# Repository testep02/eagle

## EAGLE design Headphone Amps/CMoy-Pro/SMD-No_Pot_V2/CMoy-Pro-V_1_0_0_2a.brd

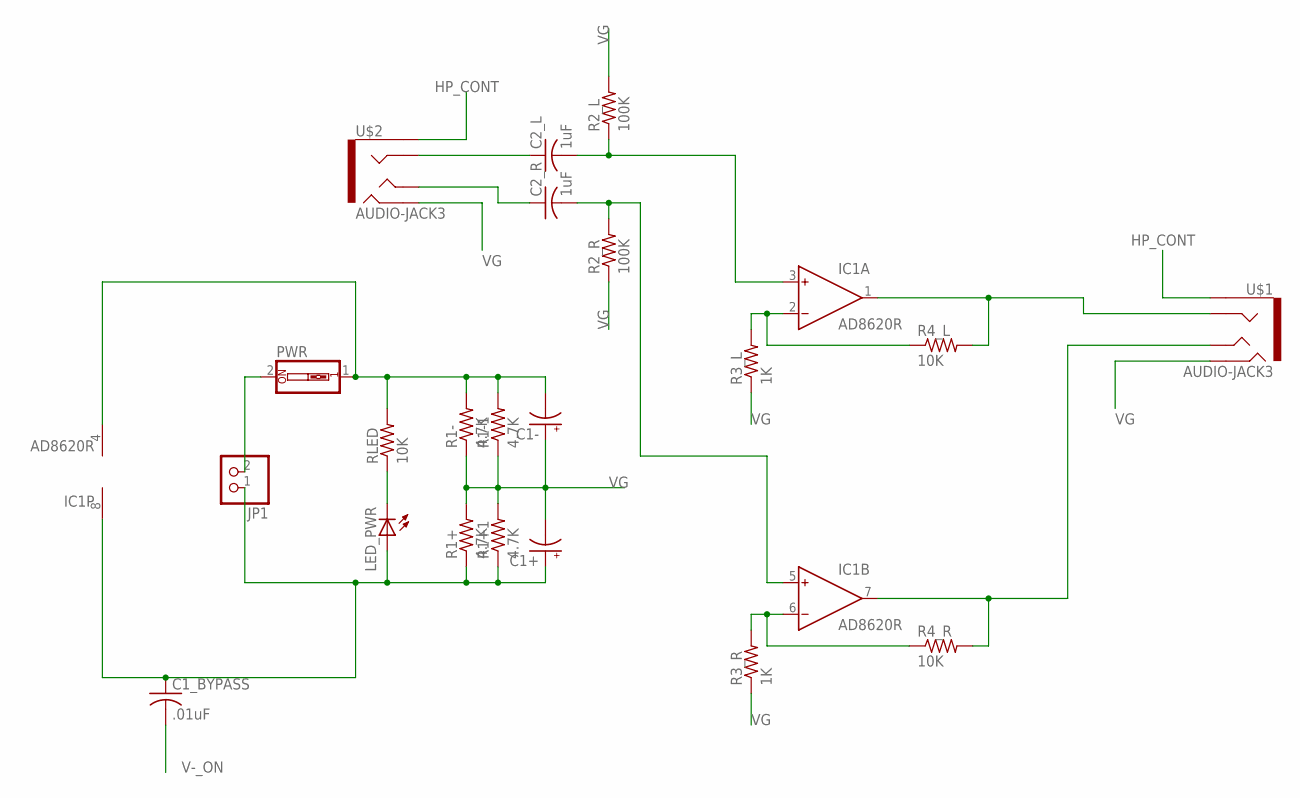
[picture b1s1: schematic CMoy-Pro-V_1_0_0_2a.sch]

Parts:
C1+, C1-: CPOL-US140CLH-0810; 140CLH-0810
C1_BYPASS: .01uF; C0603
C2_L, C2_R: 1uF; C1210
IC1: AD8620R; SO8
JP1: PINHD-1X2; 1X02
LED_PWR: LEDCHIP-LED0603; CHIP-LED0603
PWR: SW_DIP-1; EDG-01
R1+, R1+1, R1-, R1-1: 4.7K; R0603
R2_L, R2_R: 100K; R0603
R3_L, R3_R: 1K; R0603
R4_L, R4_R: 10K; R0603
RLED: 10K; R0603
U$1, U$2: AUDIO-JACK3; AUDIO-JACK-TRRS-SMD

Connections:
HP_CONT: U$1.EARTH, U$2.EARTH
HP_L: C2_R.1, U$2.TIP
HP_R: C2_L.1, U$2.RING1
IN_L: C2_R.2, IC1.5 (IN+), R2_R.2
IN_R: C2_L.2, IC1.3 (IN+), R2_L.1
unnamed: LED_PWR.C, RLED.1
unnamed: IC1.2 (IN-), R3_L.2, R4_L.1
unnamed: IC1.6 (IN-), R3_R.2, R4_R.1
OUT_L: IC1.7 (OUT), R4_R.2, U$1.TIP
OUT_R: IC1.1 (OUT), R4_L.2, U$1.RING1
V+: C1+.+, C1_BYPASS.1, IC1.8 (V+), JP1.1, LED_PWR.A, R1+.1, R1+1.1
V-: JP1.2, PWR.2
V-_ON: C1-.-, C1_BYPASS.2, IC1.4 (V-), PWR.1, R1-.2, R1-1.2, RLED.2
VG: C1+.-, C1-.+, R1+.2, R1+1.2, R1-.1, R1-1.1, R2_L.2, R2_R.1, R3_L.1, R3_R.1, U$1.RING2, U$2.RING2

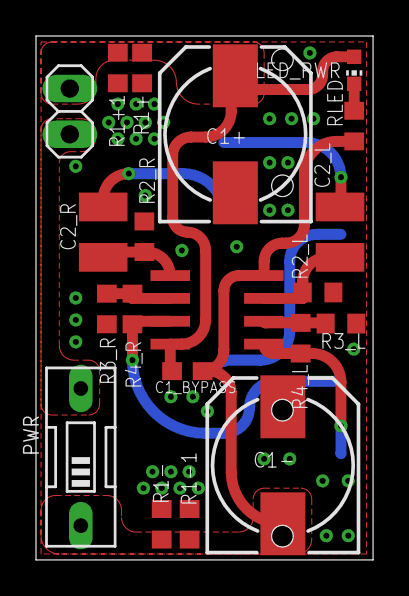
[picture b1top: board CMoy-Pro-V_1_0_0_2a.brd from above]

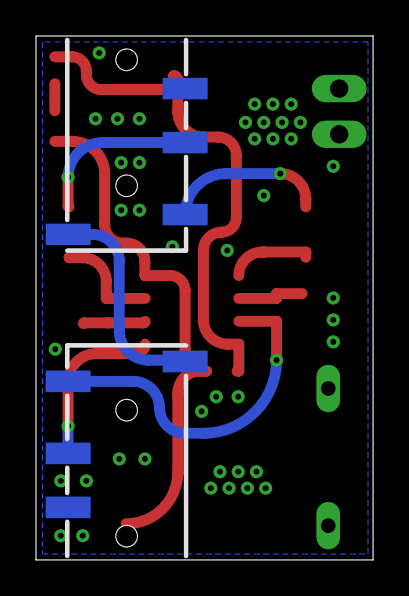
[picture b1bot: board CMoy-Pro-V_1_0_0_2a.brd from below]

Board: 2 copper layers, 18.7 x 29.1 mm, 22 parts (2 on the bottom side), 14 nets.

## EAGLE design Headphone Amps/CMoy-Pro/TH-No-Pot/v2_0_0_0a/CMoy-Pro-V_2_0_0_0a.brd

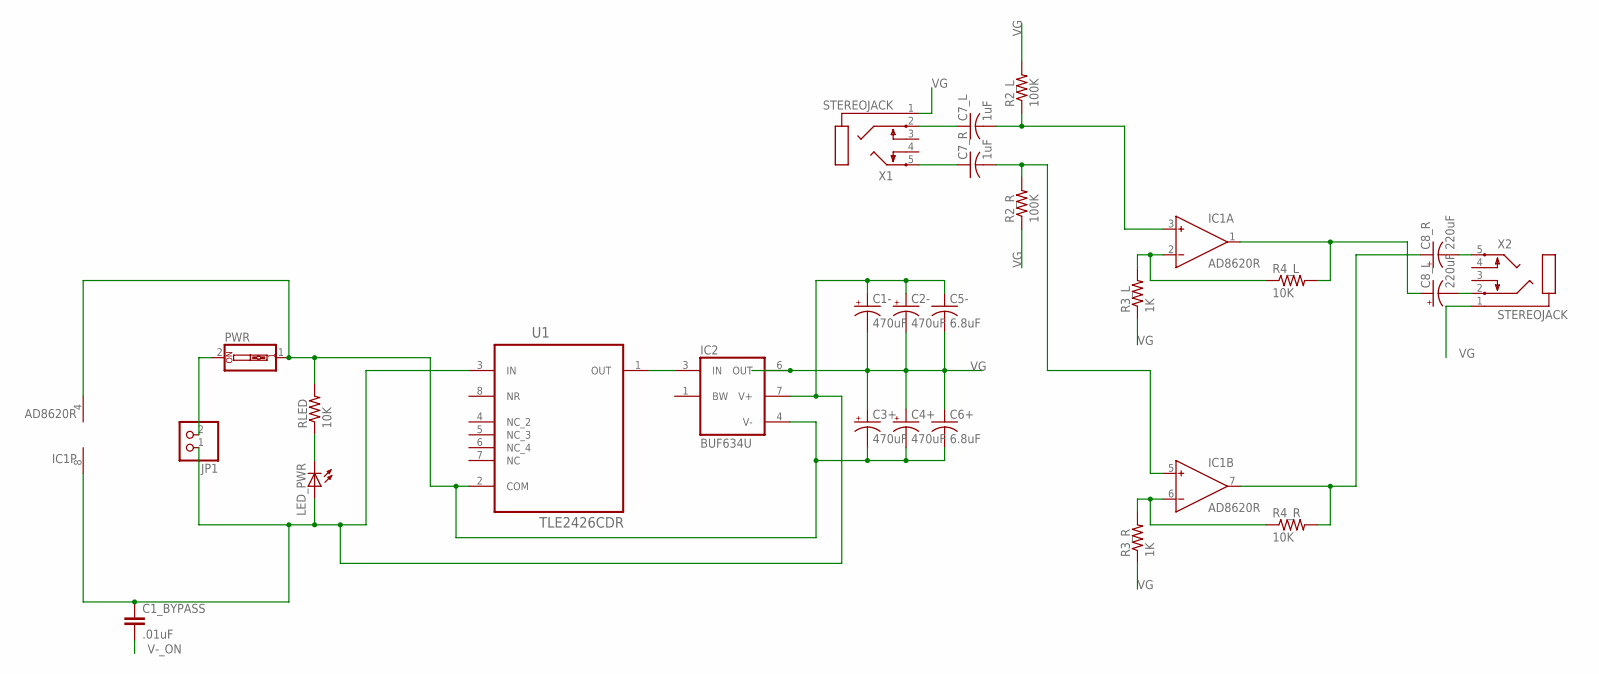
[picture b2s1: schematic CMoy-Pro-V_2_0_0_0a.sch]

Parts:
C1-, C2-, C3+, C4+: 470uF; E3,5-10
C1_BYPASS: .01uF; C0402
C5-, C6+: 6.8uF; C075-042X103
C7_L, C7_R: 1uF; C075-042X103
C8_L, C8_R: 220uF; E3,5-10
IC1: AD8620R; SO8
IC2: BUF634U; SO08
JP1: PINHD-1X2; 1X02
LED_PWR: LED3MM
PWR: SW_DIP-1; EDG-01
R2_L, R2_R: 100K; 0207/7
R3_L, R3_R: 1K; 0207/7
R4_L, R4_R: 10K; 0207/7
RLED: 10K; 0207/7
U1: TLE2426CDR; SOIC127P600X175-8N
X1, X2: STEREOJACK; STX3100

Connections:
IN_R: C7_R.2, IC1.5 (IN+), R2_R.2
unnamed: C7_L.2, IC1.3 (IN+), R2_L.1
unnamed: C8_L.-, X2.2
unnamed: LED_PWR.K (C), RLED.1
unnamed: C7_L.1, X1.2
unnamed: IC1.2 (IN-), R3_L.2, R4_L.1
unnamed: IC1.6 (IN-), R3_R.2, R4_R.1
unnamed: C7_R.1, X1.5
unnamed: C8_R.-, X2.5
unnamed: IC2.3 (IN), U1.1 (OUT)
OUT_L: C8_L.+, IC1.1 (OUT), R4_L.2
OUT_R: C8_R.+, IC1.7 (OUT), R4_R.2
V+: C1-.+, C1_BYPASS.1, C2-.+, C5-.1, IC1.8 (V+), IC2.7 (V+), JP1.1, LED_PWR.A, U1.3 (IN)
V-: JP1.2, PWR.2
V-_ON: C1_BYPASS.2, C3+.-, C4+.-, C6+.2, IC1.4 (V-), IC2.4 (V-), PWR.1, RLED.2, U1.2 (COM)
VG: C1-.-, C2-.-, C3+.+, C4+.+, C5-.2, C6+.1, IC2.6 (OUT), R2_L.2, R2_R.1, R3_L.1, R3_R.1, X1.1, X2.1

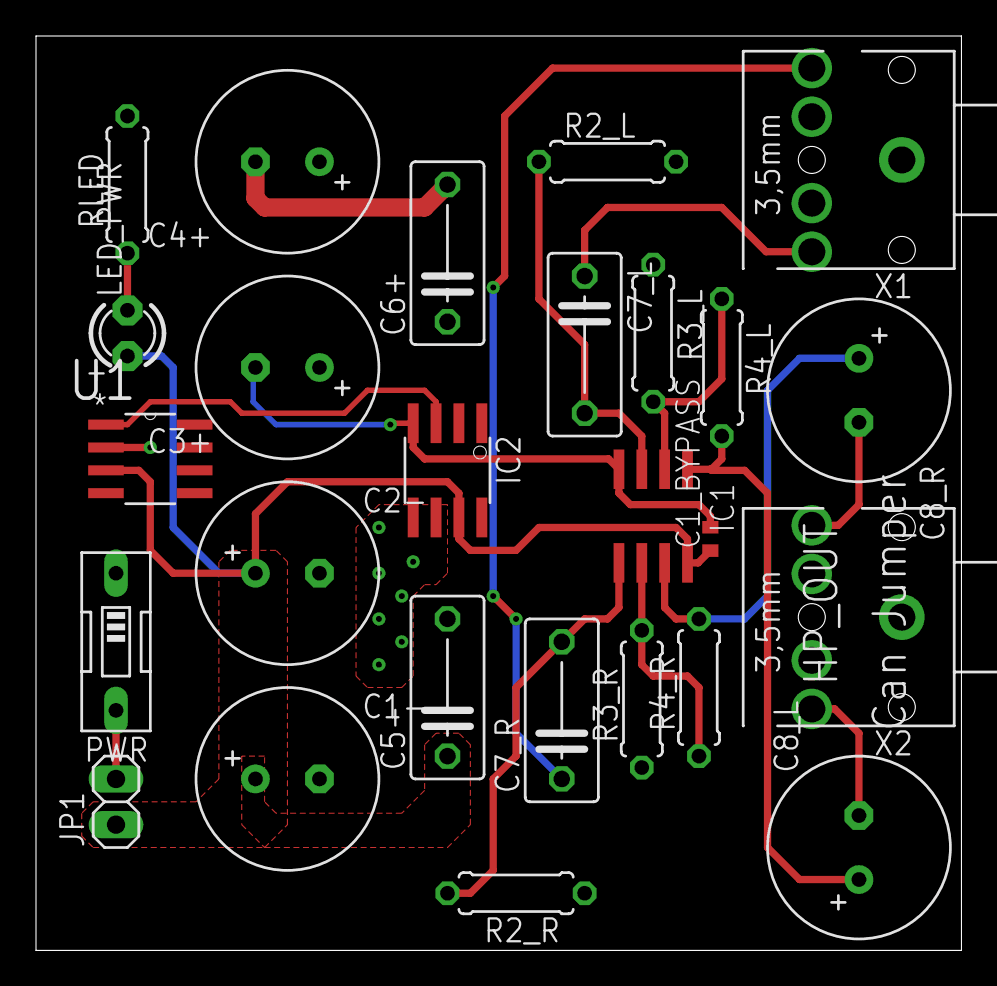
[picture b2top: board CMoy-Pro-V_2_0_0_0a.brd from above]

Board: 2 copper layers, 51.4 x 50.8 mm, 26 parts (0 on the bottom side), 16 nets.

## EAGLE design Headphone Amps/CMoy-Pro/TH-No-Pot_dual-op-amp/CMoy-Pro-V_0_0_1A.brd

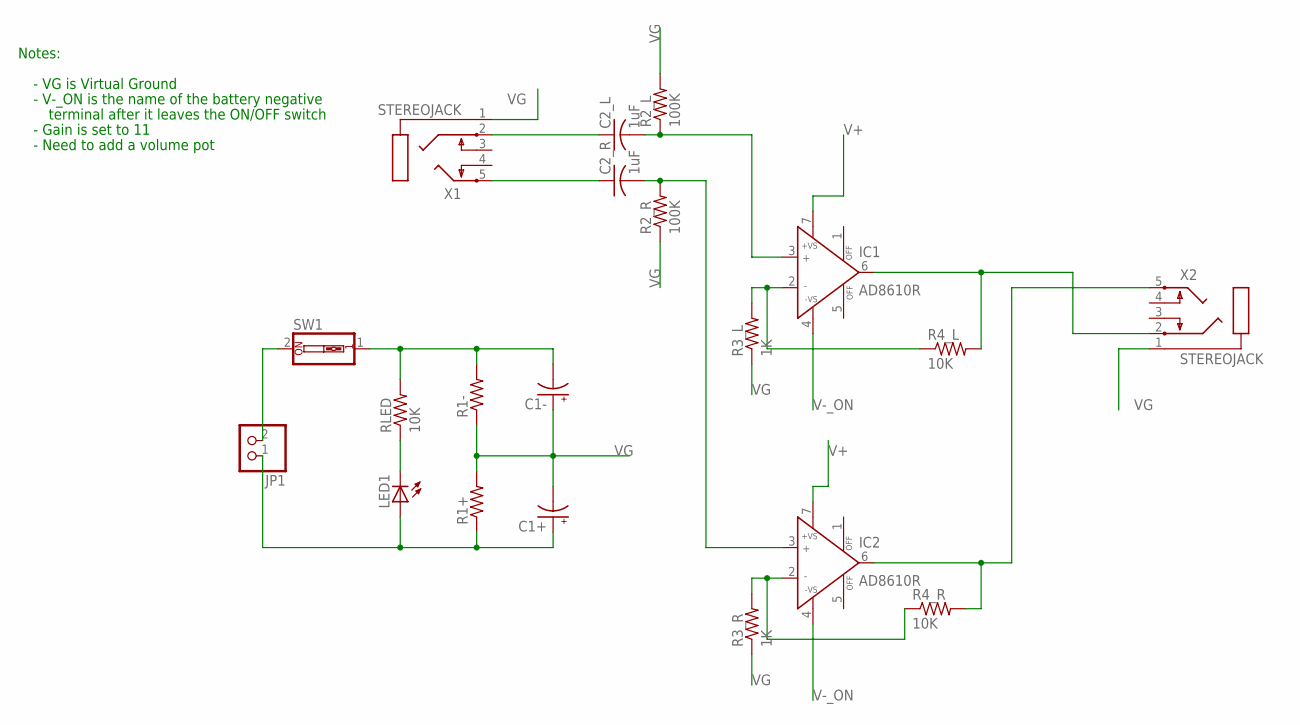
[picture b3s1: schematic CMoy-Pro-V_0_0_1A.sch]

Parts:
C1+, C1-: CPOL-USE2.5-6; E2,5-6
C2_L, C2_R: 1uF; C102-043X133
IC1, IC2: AD8610R; SO8
JP1: PINHD-1X2; 1X02
LED1: LED3MM
R1+, R1-: R-US_0207/7; 0207/7
R2_L, R2_R: 100K; 0207/7
R3_L, R3_R: 1K; 0207/7
R4_L, R4_R: 10K; 0207/7
RLED: 10K; 0207/7
SW1: SW_DIP-1; EDG-01
X1, X2: STEREOJACK; STX3100

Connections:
IN_L: C2_L.1, X1.2
IN_R: C2_R.1, X1.5
unnamed: LED1.K (C), RLED.1
unnamed: C2_L.2, IC1.3 (IN+), R2_L.1
unnamed: IC1.2 (IN-), R3_L.2, R4_L.1
unnamed: IC2.2 (IN-), R3_R.2, R4_R.1
unnamed: C2_R.2, IC2.3 (IN+), R2_R.2
OUT_L: IC1.6 (OUT), R4_L.2, X2.2
OUT_R: IC2.6 (OUT), R4_R.2, X2.5
V+: C1+.+, IC1.7 (+VS), IC2.7 (+VS), JP1.1, LED1.A, R1+.1
V-: JP1.2, SW1.2
V-_ON: C1-.-, IC1.4 (-VS), IC2.4 (-VS), R1-.2, RLED.2, SW1.1
VG: C1+.-, C1-.+, R1+.2, R1-.1, R2_L.2, R2_R.1, R3_L.1, R3_R.1, X1.1, X2.1

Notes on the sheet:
Notes:
- VG is Virtual Ground
- V-_ON is the name of the battery negative
terminal after it leaves the ON/OFF switch
- Gain is set to 11
- Need to add a volume pot

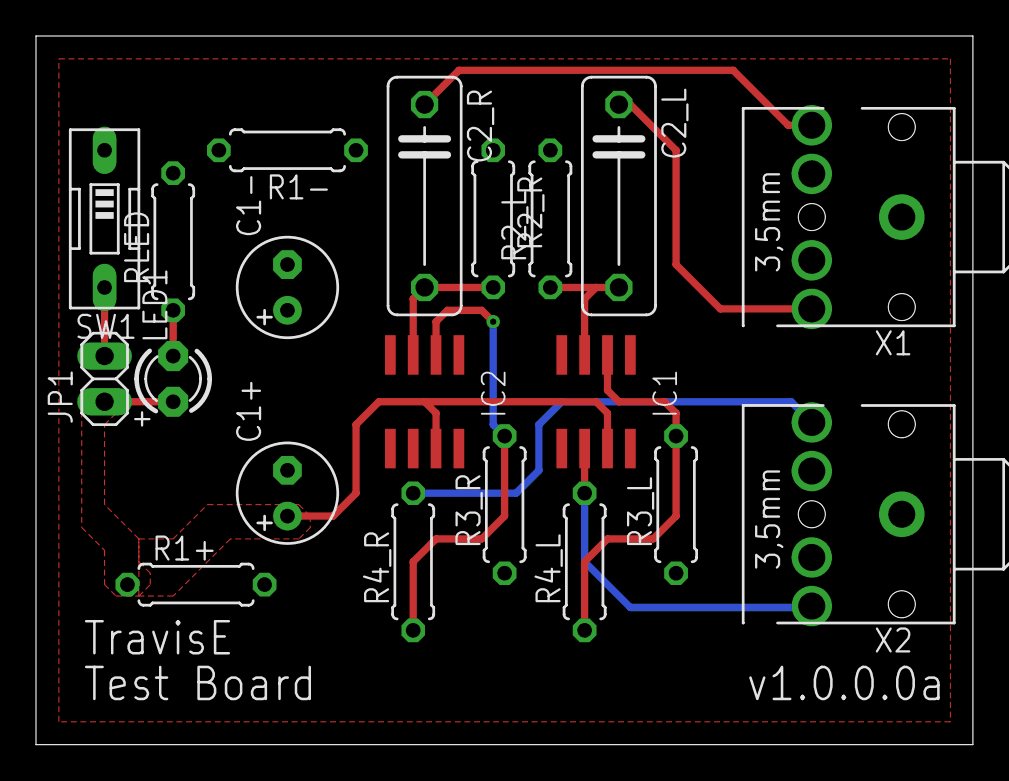
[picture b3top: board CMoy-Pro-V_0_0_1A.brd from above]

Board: 2 copper layers, 52.1 x 39.4 mm, 20 parts (0 on the bottom side), 13 nets.

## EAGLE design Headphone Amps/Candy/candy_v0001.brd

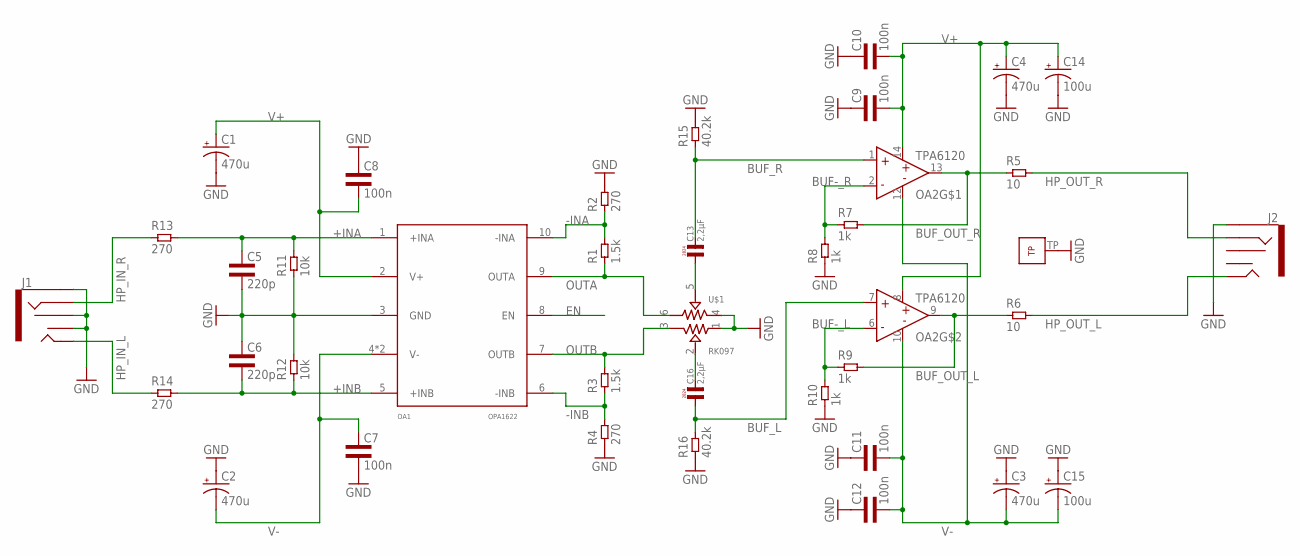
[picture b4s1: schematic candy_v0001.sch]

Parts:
C1, C2, C3, C4: 470u; PANASONIC_F
C5, C6: 220p; 0805L3
C7, C8, C9, C10, C11, C12: 100n; 0603L3
C13, C16: 2,2µF; L7,2
C14, C15: 100u; PANASONIC_D
J1, J2: AUDIO-JACK2SMD; AUDIO-JACK-3.5MM-SMD
OA1: OPA1622; S-PVSON-N10
OA2: TPA6120QFN; S-PVQFN-N14
R1, R3: 1.5k; 0603L3
R2, R4, R13, R14: 270; 0603L3
R5, R6: 10; 1206L3
R7, R8, R9, R10: 1k; 0603L3
R11, R12: 10k; 0603L3
R15, R16: 40.2k; 0603L3
U$1: RK097

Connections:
+INA: C5.1, OA1.1 (+INA), R11.P$2 (2), R13.P$2 (2)
+INB: C6.2, OA1.5 (+INB), R12.P$1 (1), R14.P$2 (2)
-INA: OA1.10 (-INA), R1.P$2 (2), R2.P$1 (1)
-INB: OA1.6 (-INB), R3.P$1 (1), R4.P$2 (2)
BUF-_L: OA2.6 (IN-), R9.P$1 (1), R10.P$2 (2)
BUF-_R: OA2.2 (IN-), R7.P$1 (1), R8.P$2 (2)
BUF_L: C16.P$1 (1), OA2.7 (IN+), R16.P$2 (2)
BUF_OUT_L: OA2.9 (OUT), R6.1, R9.P$2 (2)
BUF_OUT_R: OA2.13 (OUT), R5.1, R7.P$2 (2)
BUF_R: C13.P$2 (2), OA2.1 (IN+), R15.P$1 (1)
EN: OA1.8 (EN)
GND: C1.-, C2.+, C3.+, C4.-, C5.2, C6.1, C7.P$2 (2), C8.P$1 (1), C9.P$1 (1), C10.P$1 (1), C11.P$1 (1), C12.P$1 (1), C14.-, C15.+, J1.RSH, J1.SLEEVE, J1.TSH, J2.SLEEVE, OA1.3 (GND), OA2.TP, R2.P$2 (2), R4.P$1 (1), R8.P$1 (1), R10.P$1 (1), R11.P$1 (1), R12.P$2 (2), R15.P$2 (2), R16.P$1 (1), U$1.1, U$1.4
HP_IN_L: J1.TIP, R14.P$1 (1)
HP_IN_R: J1.RING, R13.P$1 (1)
HP_OUT_L: J2.TIP, R6.2
HP_OUT_R: J2.RING, R5.2
OUTA: OA1.9 (OUTA), R1.P$1 (1), U$1.6
OUTB: OA1.7 (OUTB), R3.P$2 (2), U$1.3
V+: C1.+, C4.+, C8.P$2 (2), C9.P$2 (2), C10.P$2 (2), C14.+, OA1.2 (V+), OA2.8 (V+), OA2.14 (V+)
V-: C2.-, C3.-, C7.P$1 (1), C11.P$2 (2), C12.P$2 (2), C15.-, OA1.4 (V-), OA1.TP (V-), OA2.10 (V-), OA2.12 (V-)
VOL_L: C16.P$2 (2), U$1.2
VOL_R: C13.P$1 (1), U$1.5

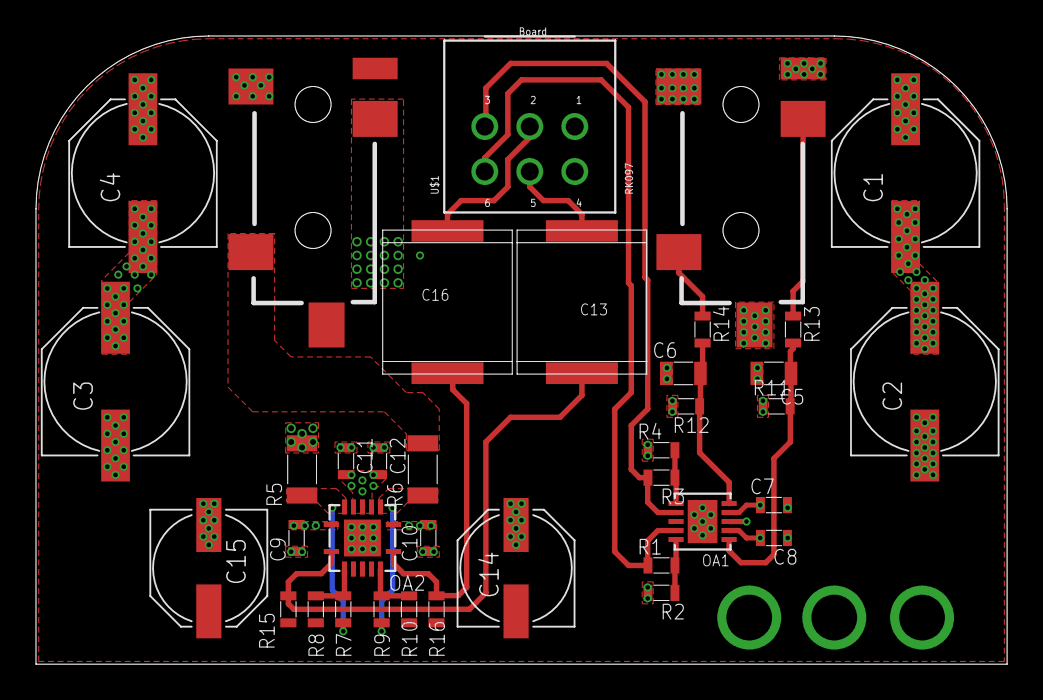
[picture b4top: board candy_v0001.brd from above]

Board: 4 copper layers, 53.9 x 34.9 mm, 37 parts (0 on the bottom side), 21 nets.

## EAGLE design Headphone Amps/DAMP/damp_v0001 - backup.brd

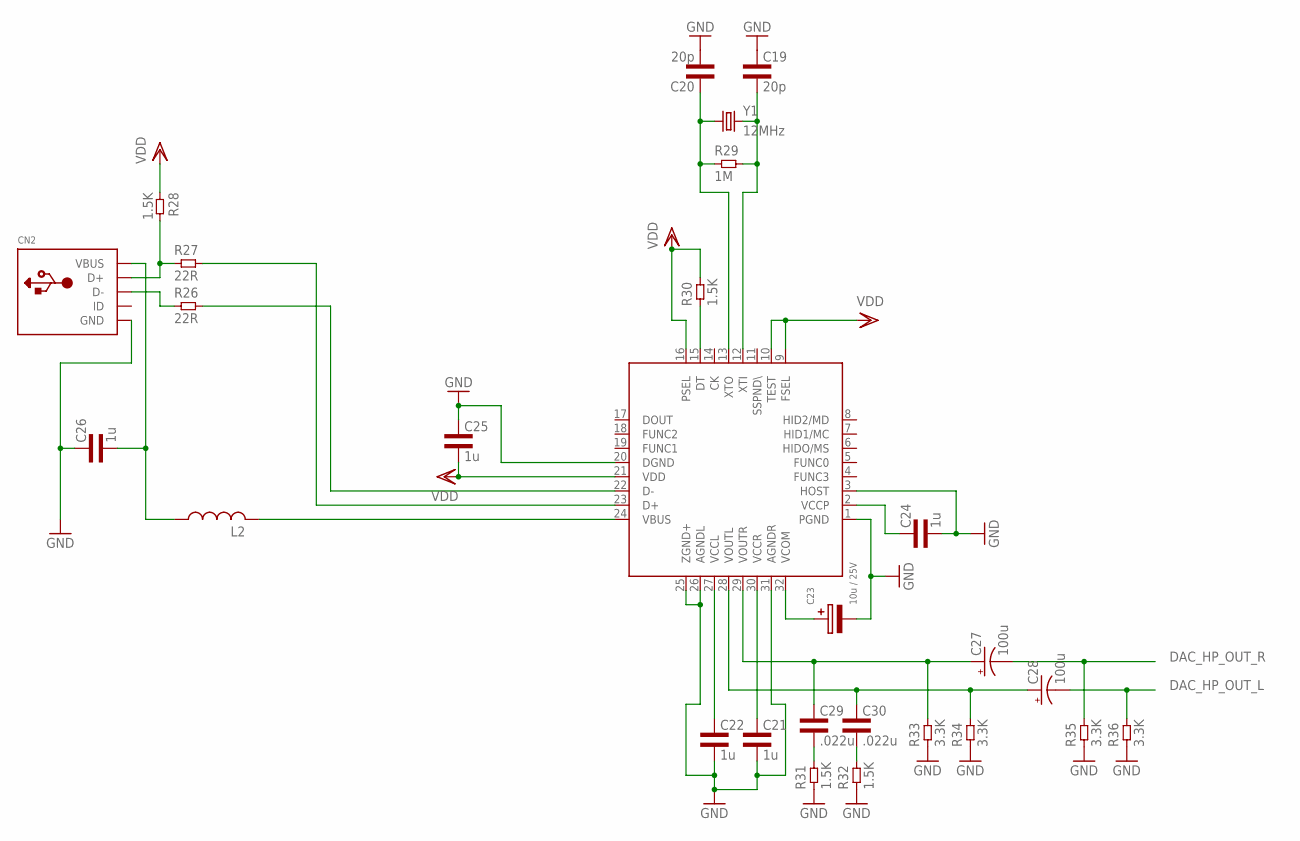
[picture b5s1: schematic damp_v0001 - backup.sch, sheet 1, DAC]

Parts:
C19, C20: 20p; 0603L3
C21, C22, C24, C25, C26: 1u; 0603L3
C23: 10u / 25V; CAP_POL_1X3
C27, C28: 100u; E2,5-7
C29, C30: .022u; 0603L3
CN2: USBMINIB; USB-MINIB
L2: RCL_L-USL3225M; RCL_L3225M
R26, R27: 22R; 0603L3
R28, R30, R31, R32: 1.5K; 0603L3
R29: 1M; 0603L3
R33, R34, R35, R36: 3.3K; 0603L3
U$1: PCM2707_V1_PCM2704C_PCM2707
Y1: 12MHz; HC49US

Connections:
DAC_HP_OUT_L: C28.-, R36.P$2 (2); also elsewhere on the board
DAC_HP_OUT_R: C27.-, R35.P$2 (2); also elsewhere on the board
GND: C19.P$1 (1), C20.P$2 (2), C21.P$2 (2), C22.P$2 (2), C23.2, C24.P$2 (2), C25.P$1 (1), C26.P$1 (1), CN2.GND, R31.P$1 (1), R32.P$1 (1), R33.P$1 (1), R34.P$1 (1), R35.P$1 (1), R36.P$1 (1), U$1.1 (PGND), U$1.3 (HOST), U$1.20 (DGND), U$1.25 (ZGND+), U$1.26 (AGNDL), U$1.31 (AGNDR); also elsewhere on the board
unnamed: CN2.D+, R27.P$1 (1), R28.P$2 (2)
unnamed: CN2.D-, R26.P$1 (1)
unnamed: R27.P$2 (2), U$1.23 (D+)
unnamed: R26.P$2 (2), U$1.22 (D-)
unnamed: C20.P$1 (1), R29.P$1 (1), U$1.13 (XTO), Y1.1
unnamed: C19.P$2 (2), R29.P$2 (2), U$1.12 (XTI), Y1.2
unnamed: C22.P$1 (1), U$1.27 (VCCL)
unnamed: C21.P$1 (1), U$1.30 (VCCR)
unnamed: C23.1, U$1.32 (VCOM)
unnamed: C29.P$2 (2), R31.P$2 (2)
unnamed: C24.P$1 (1), U$1.2 (VCCP)
unnamed: C27.+, C29.P$1 (1), R33.P$2 (2), U$1.29 (VOUTR)
unnamed: L2.2, U$1.24 (VBUS)
unnamed: C26.P$2 (2), CN2.VBUS, L2.1
unnamed: C28.+, C30.P$1 (1), R34.P$2 (2), U$1.28 (VOUTL)
unnamed: R30.P$1 (1), U$1.15 (DT)
unnamed: C30.P$2 (2), R32.P$2 (2)
VDD: C25.P$2 (2), R28.P$1 (1), R30.P$2 (2), U$1.9 (FSEL), U$1.10 (TEST), U$1.16 (PSEL), U$1.21 (VDD)

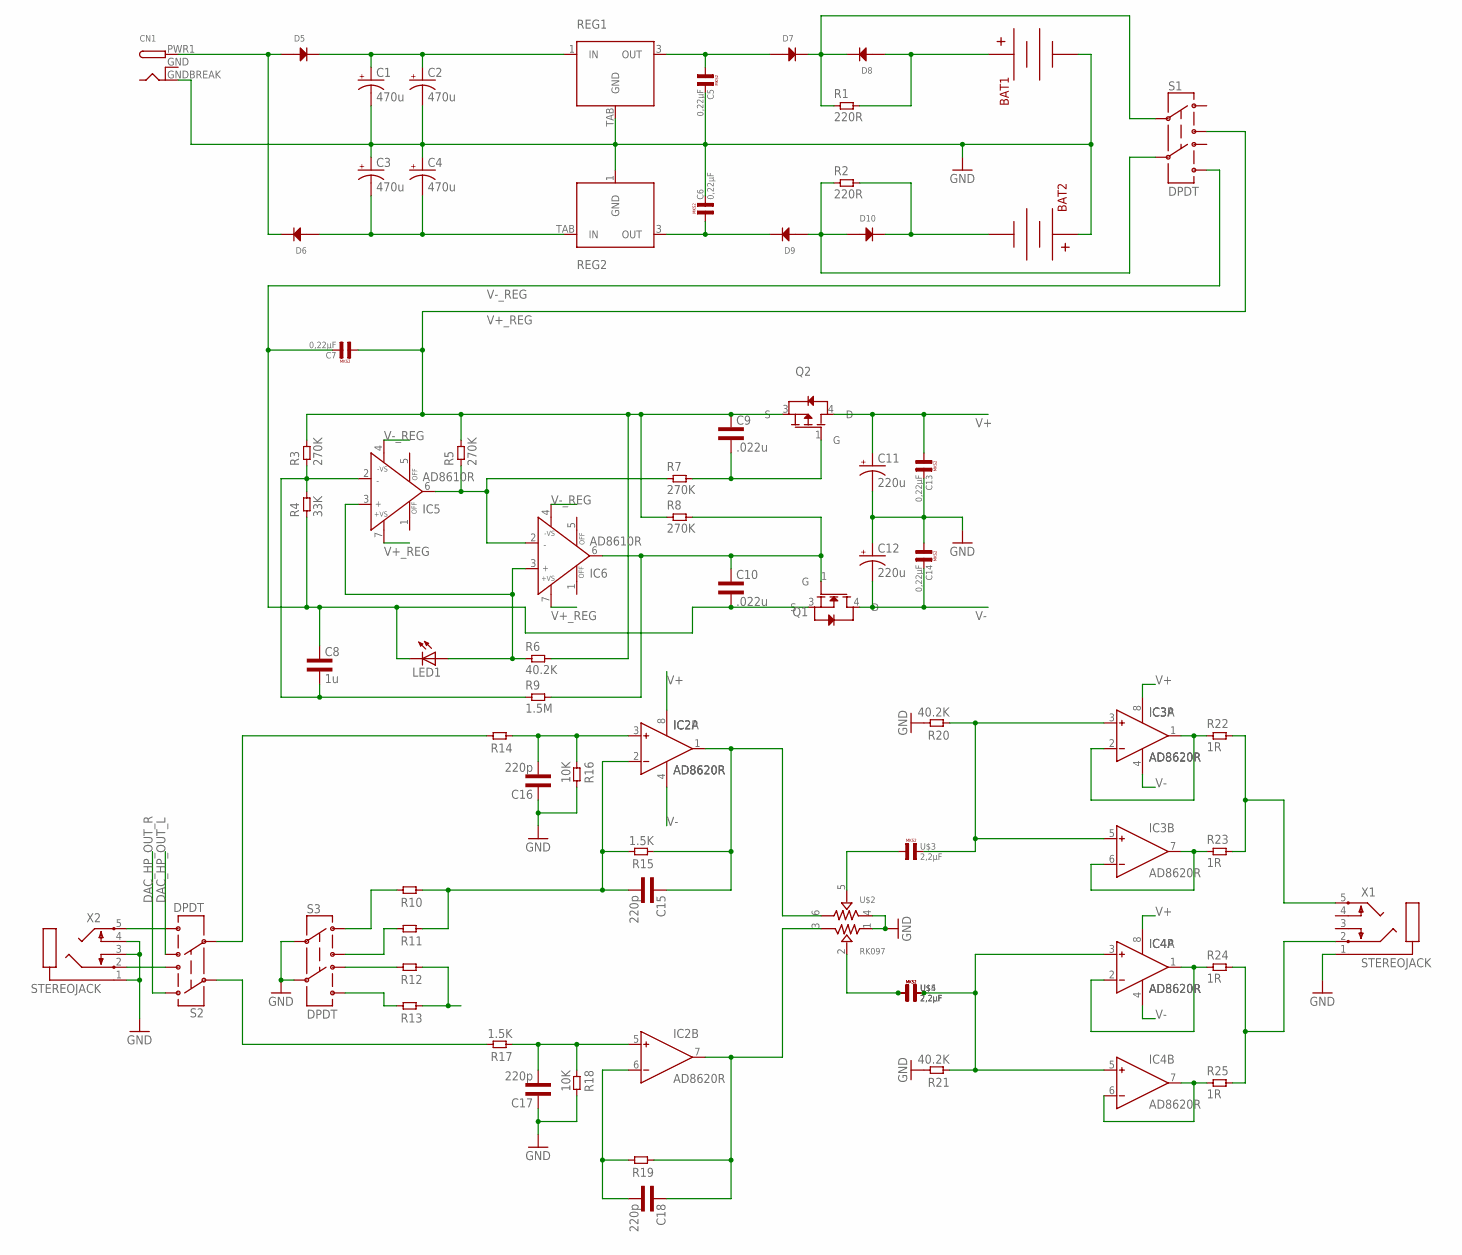
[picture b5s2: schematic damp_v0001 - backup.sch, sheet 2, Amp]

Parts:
BAT1, BAT2: BC9VPC
C1, C2, C3, C4: 470u; E5-13
C5, C6, C7, C13, C14: 0,22µF; R5B3
C8: 1u; 0603L3
C9, C10: .022u; 0603L3
C11, C12: 220u; E5-10,5
C15, C16, C17, C18: 220p; 0603L3
CN1: DCBARRELSMT; DCJACK_2MM_SMT
D5, D6, D7, D8, D9, D10: DIODEDO-214AC; DO-214AC
IC2, IC3, IC4: AD8620R; SO8
IC5, IC6: AD8610R; SO8
LED1: LEDCHIPLED_0805; CHIPLED_0805
Q1: MOSFET-N; DPAK-3
Q2: MOSFET-P; DPAK-3
R1, R2: 220R; 0603L3
R3, R5, R7, R8: 270K; 0603L3
R4: 33K; 0603L3
R6, R20, R21: 40.2K; 0603L3
R9: 1.5M; 0603L3
R10, R11, R12, R13, R14, R19: RES0603L3; 0603L3
R15, R17: 1.5K; 0603L3
R16, R18: 10K; 0603L3
R22, R23, R24, R25: 1R; 1206L3
REG1: MC7812; D2PAK
REG2: MC7912; D2PAK
S1, S2, S3: DPDT; SPARKFUN-ELECTROMECHANICAL_AYZ0202
U$2: RK097
U$3, U$4, U$5: 2,2µF; R5B7K2
X1, X2: STEREOJACK; STX3100

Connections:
DAC_HP_OUT_L: S2.4; also elsewhere on the board
DAC_HP_OUT_R: S2.1; also elsewhere on the board
GND: BAT1.V-, BAT2.V+, C1.-, C2.-, C3.+, C4.+, C5.2, C6.2, C11.-, C12.+, C13.2, C14.1, C16.P$1 (1), C17.P$1 (1), CN1.GNDBREAK (GND), R16.P$2 (2), R18.P$2 (2), R20.P$2 (2), R21.P$2 (2), REG1.TAB (GND), REG2.1 (GND), S3.2, S3.5, U$2.1, U$2.4, X1.1, X2.1, X2.3, X2.4; also elsewhere on the board
GNDBREAK: CN1.GND (GNDBREAK)
unnamed: C1.+, C2.+, D5.2 (CATHODE), REG1.1 (IN)
unnamed: C3.-, C4.-, D6.1 (ANODE), REG2.TAB (IN)
unnamed: C5.1, D7.1 (ANODE), REG1.3 (OUT)
unnamed: C6.1, D9.2 (CATHODE), REG2.3 (OUT)
unnamed: C8.P$2 (2), IC5.2 (IN-), R3.P$1 (1), R4.P$2 (2), R9.P$1 (1)
unnamed: D7.2 (CATHODE), D8.2 (CATHODE), R1.P$1 (1), S1.2
unnamed: BAT1.V+, D8.1 (ANODE), R1.P$2 (2)
unnamed: D9.1 (ANODE), D10.1 (ANODE), R2.P$1 (1), S1.5
unnamed: BAT2.V-, D10.2 (CATHODE), R2.P$2 (2)
unnamed: CN1.PWR1 (PWR), D5.1 (ANODE), D6.2 (CATHODE)
unnamed: IC5.6 (OUT), IC6.2 (IN-), R5.P$1 (1), R7.P$1 (1)
unnamed: IC5.3 (IN+), IC6.3 (IN+), LED1.A, R6.P$1 (1)
unnamed: S2.6, X2.5
unnamed: S2.3, X2.2
unnamed: C10.P$1 (1), IC6.6 (OUT), Q1.1 (G), R8.P$2 (2), R9.P$2 (2)
unnamed: C9.P$2 (2), Q2.1 (G), R7.P$2 (2)
unnamed: R14.P$2 (2), S2.5
unnamed: R17.P$2 (2), S2.2
unnamed: C17.P$2 (2), IC2.5 (IN+), R17.P$1 (1), R18.P$1 (1)
unnamed: R10.P$2 (2), S3.1
unnamed: R11.P$2 (2), S3.3
unnamed: R12.P$2 (2), S3.4
unnamed: R13.P$2 (2), S3.6
unnamed: C15.P$2 (2), IC2.2 (IN-), R10.P$1 (1), R11.P$1 (1), R15.P$2 (2)
unnamed: R12.P$1 (1), R13.P$1 (1)
unnamed: C16.P$2 (2), IC2.3 (IN+), R14.P$1 (1), R16.P$1 (1)
unnamed: C15.P$1 (1), IC2.1 (OUT), R15.P$1 (1), U$2.6
unnamed: R22.2, R23.2, X1.5
unnamed: C18.P$2 (2), IC2.6 (IN-), R19.P$2 (2)
unnamed: C18.P$1 (1), IC2.7 (OUT), R19.P$1 (1), U$2.3
unnamed: R24.2, R25.2, X1.2
unnamed: U$2.2, U$4.1, U$5.1
unnamed: IC4.3 (IN+), IC4.5 (IN+), R21.P$1 (1), U$4.2, U$5.2
unnamed: U$2.5, U$3.1
unnamed: IC3.3 (IN+), IC3.5 (IN+), R20.P$1 (1), U$3.2
unnamed: IC3.1 (OUT), IC3.2 (IN-), R22.1
unnamed: IC3.6 (IN-), IC3.7 (OUT), R23.1
unnamed: IC4.1 (OUT), IC4.2 (IN-), R24.1
unnamed: IC4.6 (IN-), IC4.7 (OUT), R25.1
V+: C11.+, C13.1, IC2.8 (V+), IC3.8 (V+), IC4.8 (V+), Q2.4 (D)
V+_REG: C7.1, C9.P$1 (1), IC5.7 (+VS), IC6.7 (+VS), Q2.3 (S), R3.P$2 (2), R5.P$2 (2), R6.P$2 (2), R8.P$1 (1), S1.3
V-: C12.-, C14.2, IC2.4 (V-), IC3.4 (V-), IC4.4 (V-), Q1.4 (D)
V-_REG: C7.2, C8.P$1 (1), C10.P$2 (2), IC5.4 (-VS), IC6.4 (-VS), LED1.C, Q1.3 (S), R4.P$1 (1), S1.6

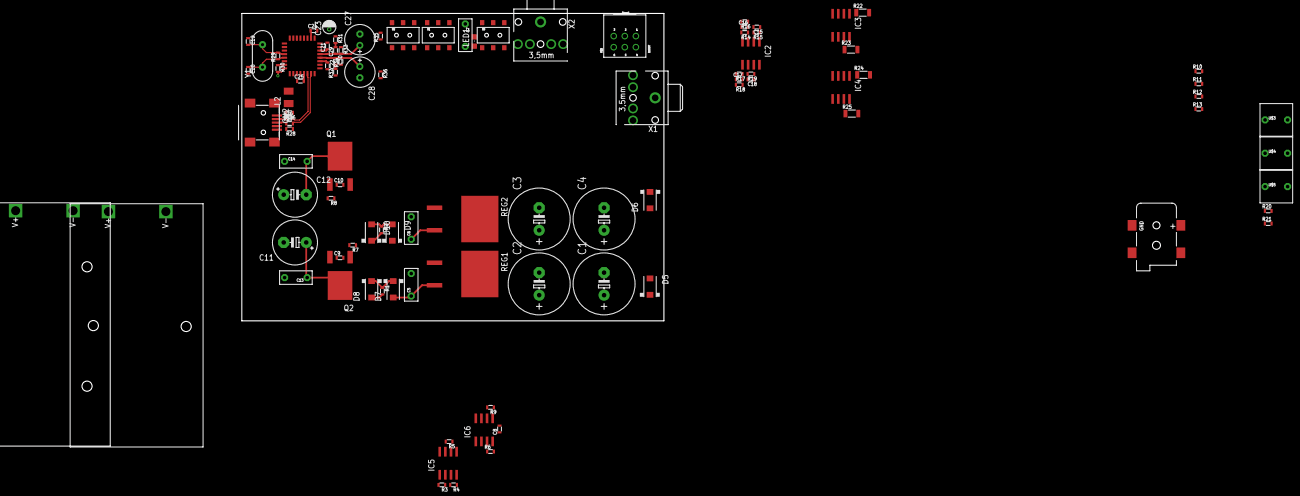
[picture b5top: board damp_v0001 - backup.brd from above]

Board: 2 copper layers, 95.2 x 69.3 mm, 98 parts (0 on the bottom side), 64 nets.

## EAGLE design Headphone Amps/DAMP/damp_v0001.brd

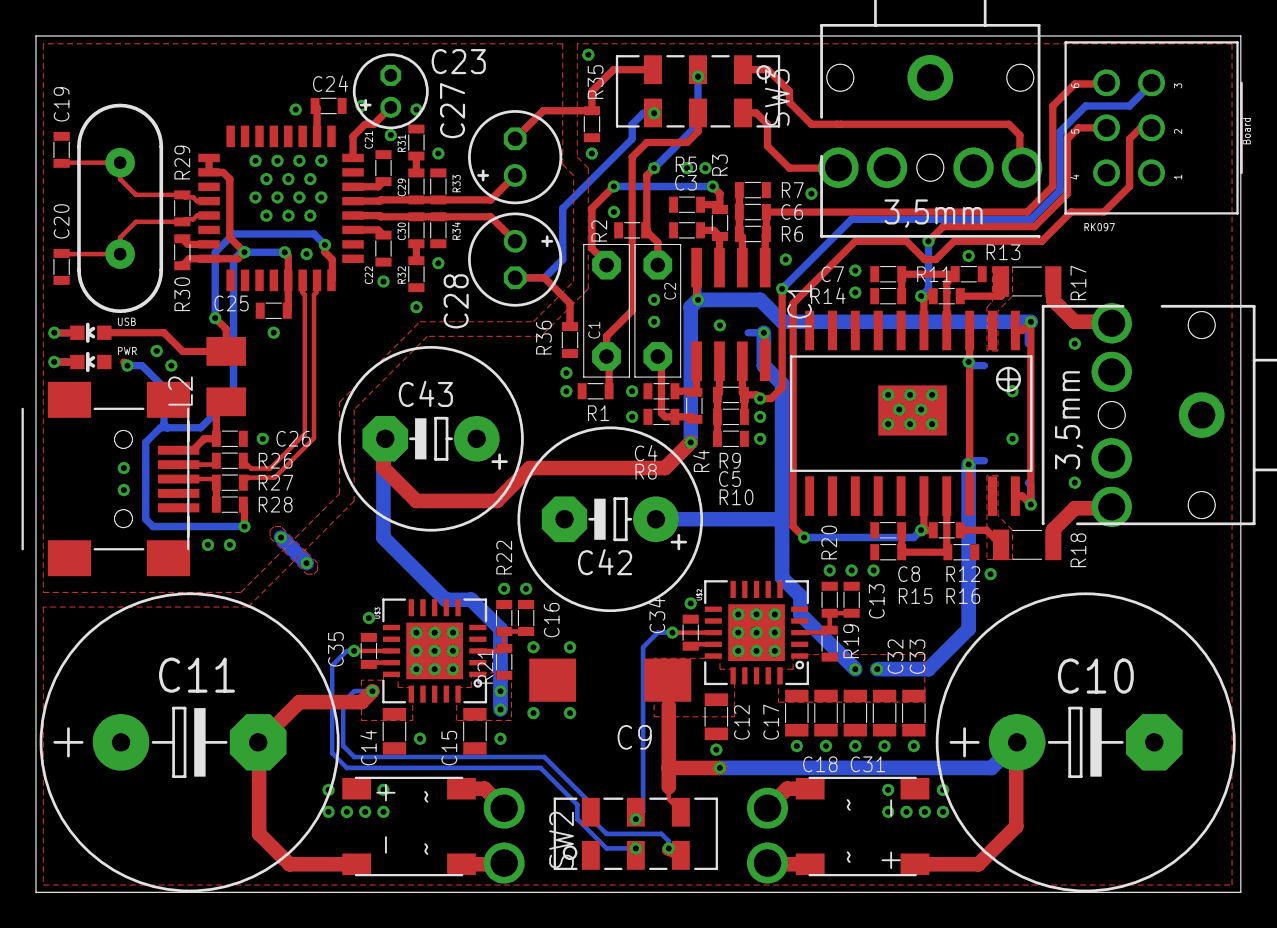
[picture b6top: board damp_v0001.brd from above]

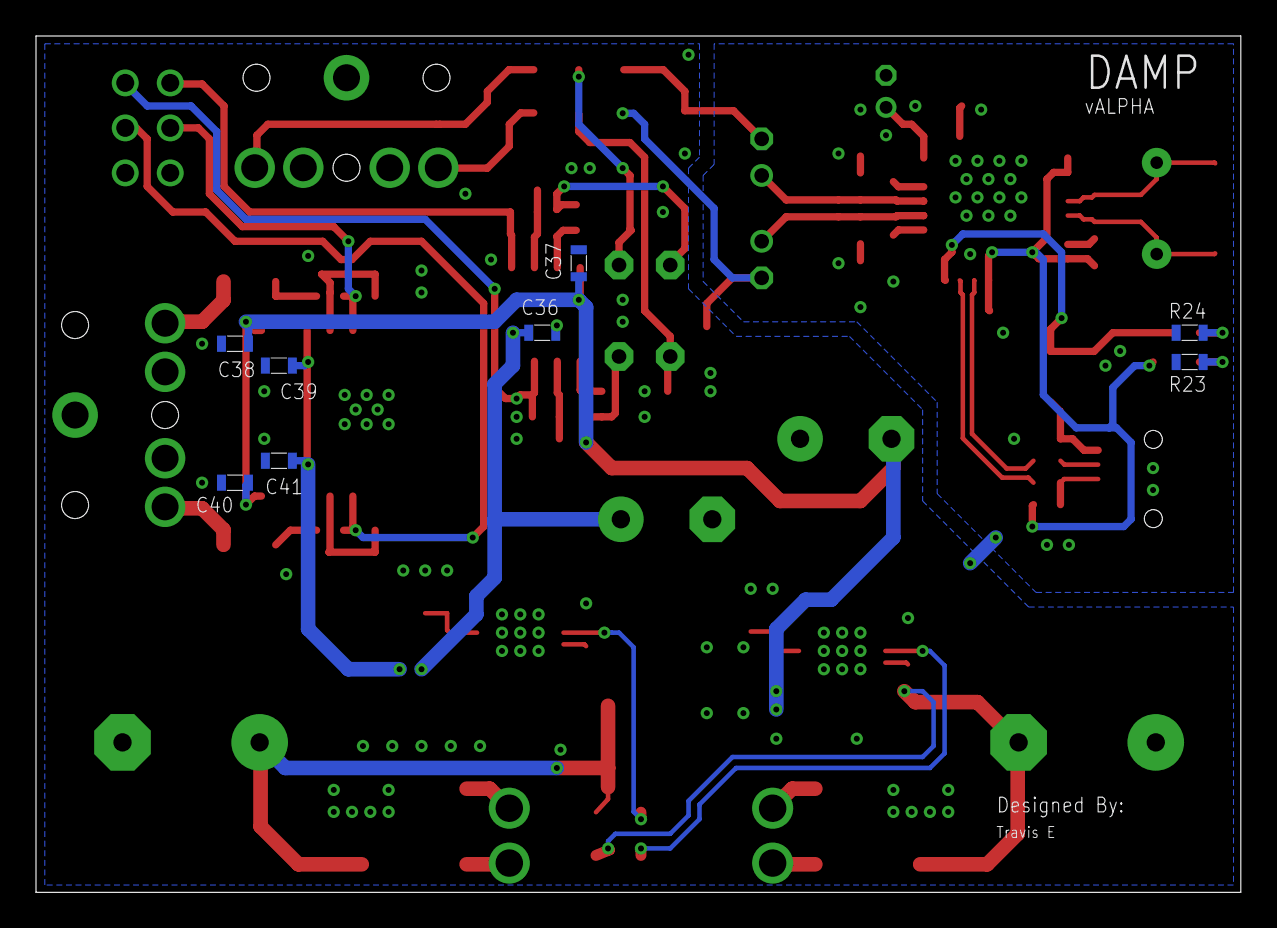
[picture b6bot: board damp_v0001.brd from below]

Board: 2 copper layers, 66.9 x 47.6 mm, 95 parts (8 on the bottom side), 53 nets.

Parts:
C1, C2: 0,1µF; R5B2K5
C3, C4: 100p; 0603L3
C5, C6: 220p; 0603L3
C7, C8, C38, C39, C40, C41: 100n; 0603L3
C9: 47u; CT7343
C10, C11: 1000u; E7,5-16
C12, C14, C15, C17, C18, C31, C32, C33: 10u; 0805L3
C13, C21, C22, C24, C25, C26, C34: 1u; 0603L3
C16, C35: 10n; 0603L3
C19, C20: 20p; 0603L3
C23: 10u / 25V; E1,8-4
C27, C28: 100u; E2-5
C29, C30: .022u; 0603L3
C36, C37: 0603L3
C42, C43: 470u; E5-10,5
CN2: USB-MINIB
IC1: AD8620R; SO8
L2: RCL_L3225M
PWR: BLUE; LED-0603
R1, R2, R5, R8: 470K; 0603L3
R3, R4, R11, R12, R13, R14, R15, R16: 1K0; 0603L3
R6, R9, R23, R24, R28, R30: 1.5K; 0603L3
R7, R10: 499R; 0603L3
R17, R18: 10R; 1206L3
R19: 102k; 0603L3
R20: 10.5k; 0603L3
R21: 1.24M; 0603L3
R22: 105K; 0603L3
R26, R27: 22R; 0603L3
R29: 1M; 0603L3
R31, R32: 16R; 0603L3
R33, R34, R35, R36: 3.3K; 0603L3
RECT1, RECT2: RECTIFIER_ABS-4
SW2, SW3: CAS-A
U$1: PCM2707_V1_PCM2704C_PCM2707
U$2: POWER-SUPPLY_POS_V1_TI_LDO_TPS7A4700; POWER-SUPPLY_POS_V1_TI_LDO_VQFN-20
U$3: POWER-SUPPLY_POS_V1_TI_LDO_TPS7A3301RGWT; POWER-SUPPLY_POS_V1_TI_LDO_VQFN-20
U$4: PCM2707_V1_AMP_TPA6120_TPA6120
U$5: RK097
USB: BLUE; LED-0603
X1, X2: STEREOJACK; STX3100
Y1: 12MHz; HC49US

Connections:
DAC_HP_OUT_L: C28.-, R36.P$2, SW3.P$6
DAC_HP_OUT_R: C27.-, R35.P$2, SW3.P$3
GND: C3.P$2, C4.P$2, C7.P$1, C8.P$2, C9.-, C10.-, C11.+, C12.2, C13.P$1, C14.2, C15.2, C16.P$1, C17.2, C18.2, C19.P$1, C20.P$2, C21.P$2, C22.P$2, C23.-, C24.P$2, C25.P$1, C26.P$1, C31.2, C32.2, C33.2, C34.P$2, C35.P$2, C36.P$2, C37.P$2, C38.P$2, C39.P$2, C40.P$1, C41.P$1, C42.-, C43.+, CN2.GND, R1.P$2, R2.P$2, R5.P$2, R7.P$1, R8.P$2, R10.P$1, R13.P$1, R14.P$1, R15.P$1, R16.P$1, R20.P$2, R22.P$2, R23.P$1, R24.P$2, R31.P$1, R32.P$1, R33.P$1, R34.P$1, R35.P$1, R36.P$1, RECT1.4, RECT2.1, U$1.1, U$1.3, U$1.20, U$1.25, U$1.26, U$1.31, U$2.7, U$2.TP, U$3.7, U$3.TP, U$4.6, U$4.7, U$4.8, U$4.9, U$4.10, U$4.11, U$4.12, U$4.13, U$4.14, U$4.15, U$4.21, U$5.1, U$5.4, X1.1, X1.3, X1.4, X2.1
unnamed: SW3.P$4, X1.5
unnamed: PWR.C, R23.P$2
unnamed: SW3.P$1, X1.2
unnamed: C34.P$1, U$2.14
unnamed: R24.P$1, USB.C
unnamed: C1.2, R3.P$1, R5.P$1
unnamed: C3.P$1, IC1.3, R3.P$2
unnamed: C6.P$2, IC1.2, R6.P$1, R7.P$2
unnamed: R11.P$1, U$4.5, U$5.5
unnamed: R12.P$1, U$4.16, U$5.2
unnamed: C2.2, R4.P$1, R8.P$1
unnamed: C4.P$1, IC1.5, R4.P$2
unnamed: R11.P$2, R17.2, U$4.2
unnamed: C5.P$2, IC1.6, R9.P$1, R10.P$2
unnamed: R12.P$2, R18.1, U$4.19
unnamed: C7.P$2, R13.P$2, R14.P$2, U$4.4
unnamed: CN2.D+, R27.P$1, R28.P$2
unnamed: C8.P$1, R15.P$2, R16.P$2, U$4.17
unnamed: R17.1, X2.5
unnamed: CN2.D-, R26.P$1
unnamed: R18.2, X2.2
unnamed: C13.P$2, R19.P$2, R20.P$1, U$2.3
unnamed: C16.P$2, R21.P$2, R22.P$1, U$3.3
unnamed: C35.P$1, U$3.14
unnamed: R27.P$2, U$1.23
unnamed: R26.P$2, U$1.22
unnamed: C20.P$1, R29.P$1, U$1.13, Y1.1
unnamed: C19.P$2, R29.P$2, U$1.12, Y1.2
unnamed: C22.P$1, U$1.27
unnamed: C21.P$1, U$1.30
unnamed: C23.+, U$1.32
unnamed: C29.P$2, R31.P$2
unnamed: C24.P$1, U$1.2
unnamed: C27.+, C29.P$1, R33.P$2, U$1.29
unnamed: L2.2, U$1.24, USB.A
unnamed: C26.P$2, CN2.VBUS, L2.1
unnamed: C28.+, C30.P$1, R34.P$2, U$1.28
unnamed: R30.P$1, U$1.15
unnamed: C30.P$2, R32.P$2
NEG_EN: SW2.P$2, U$3.13
NEG_RAW: C11.-, C14.1, RECT2.4, SW2.P$3, U$3.15, U$3.16
OA_IN_L: C1.1, R1.P$1, SW3.P$5
OA_IN_R: C2.1, R2.P$1, SW3.P$2
OA_OUT_L: C6.P$1, IC1.1, R6.P$2, U$5.6
OA_OUT_R: C5.P$1, IC1.7, R9.P$2, U$5.3
POS_EN: SW2.P$5, U$2.13
POS_RAW: C9.+, C10.+, C12.1, RECT1.1, SW2.P$6, U$2.15, U$2.16
V+: C17.1, C18.1, C31.1, C32.1, C33.1, C36.P$1, C39.P$1, C41.P$2, C42.+, IC1.8, R19.P$1, U$2.1, U$2.20, U$4.3, U$4.18
V-: C15.1, C37.P$1, C38.P$1, C40.P$2, C43.-, IC1.4, R21.P$1, U$3.1, U$3.20, U$4.1, U$4.20
VDD: C25.P$2, PWR.A, R28.P$1, R30.P$2, U$1.9, U$1.10, U$1.16, U$1.21

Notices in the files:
parts and their libraries:
SparkFun-Connectors: Licensing: CC v3.0 Share-Alike You are welcome to use this library for commercial purposes.
SparkFun-FreqCtrl: Licensing: CC
SparkFun-Electromechanical: Licensing: CC v3.0 Share-Alike You are
